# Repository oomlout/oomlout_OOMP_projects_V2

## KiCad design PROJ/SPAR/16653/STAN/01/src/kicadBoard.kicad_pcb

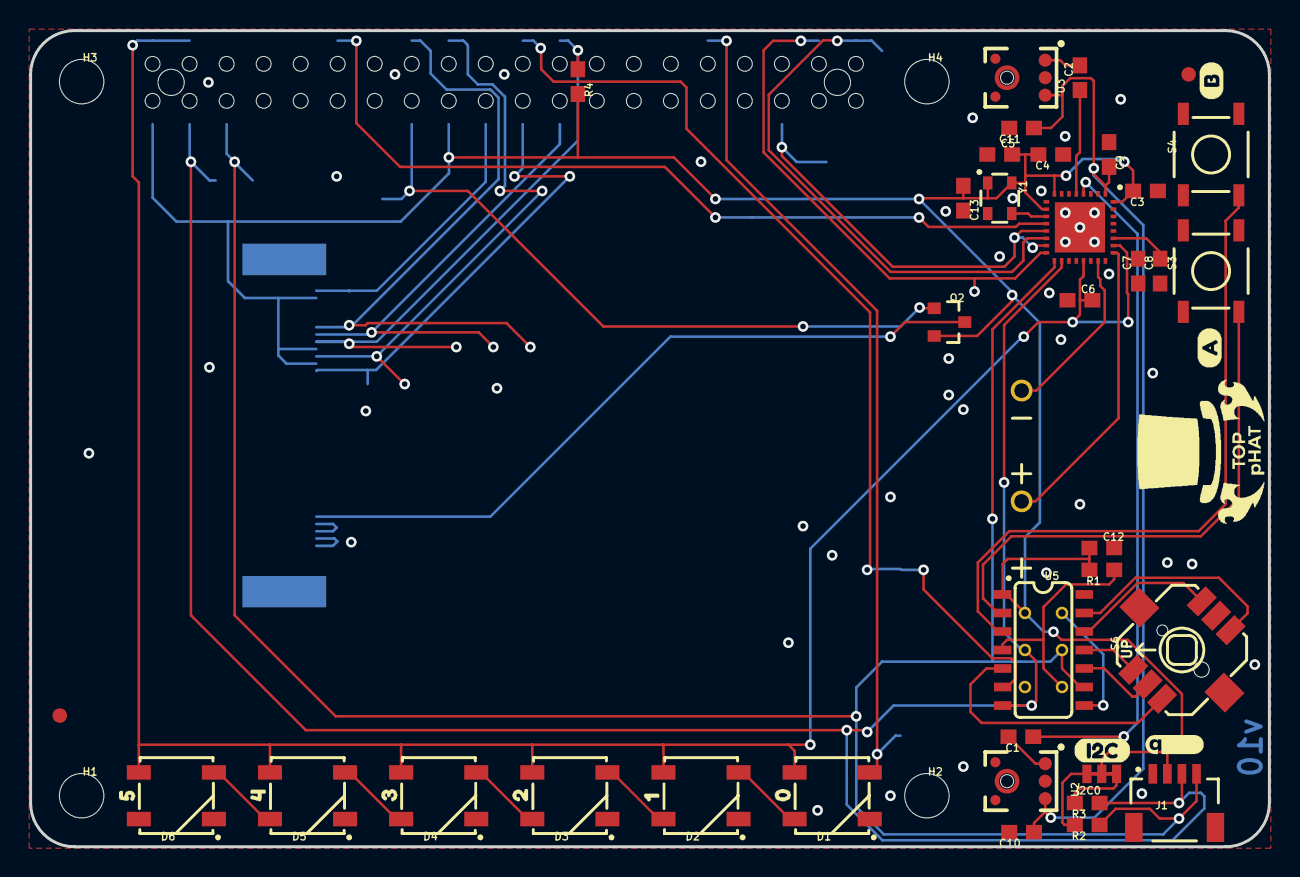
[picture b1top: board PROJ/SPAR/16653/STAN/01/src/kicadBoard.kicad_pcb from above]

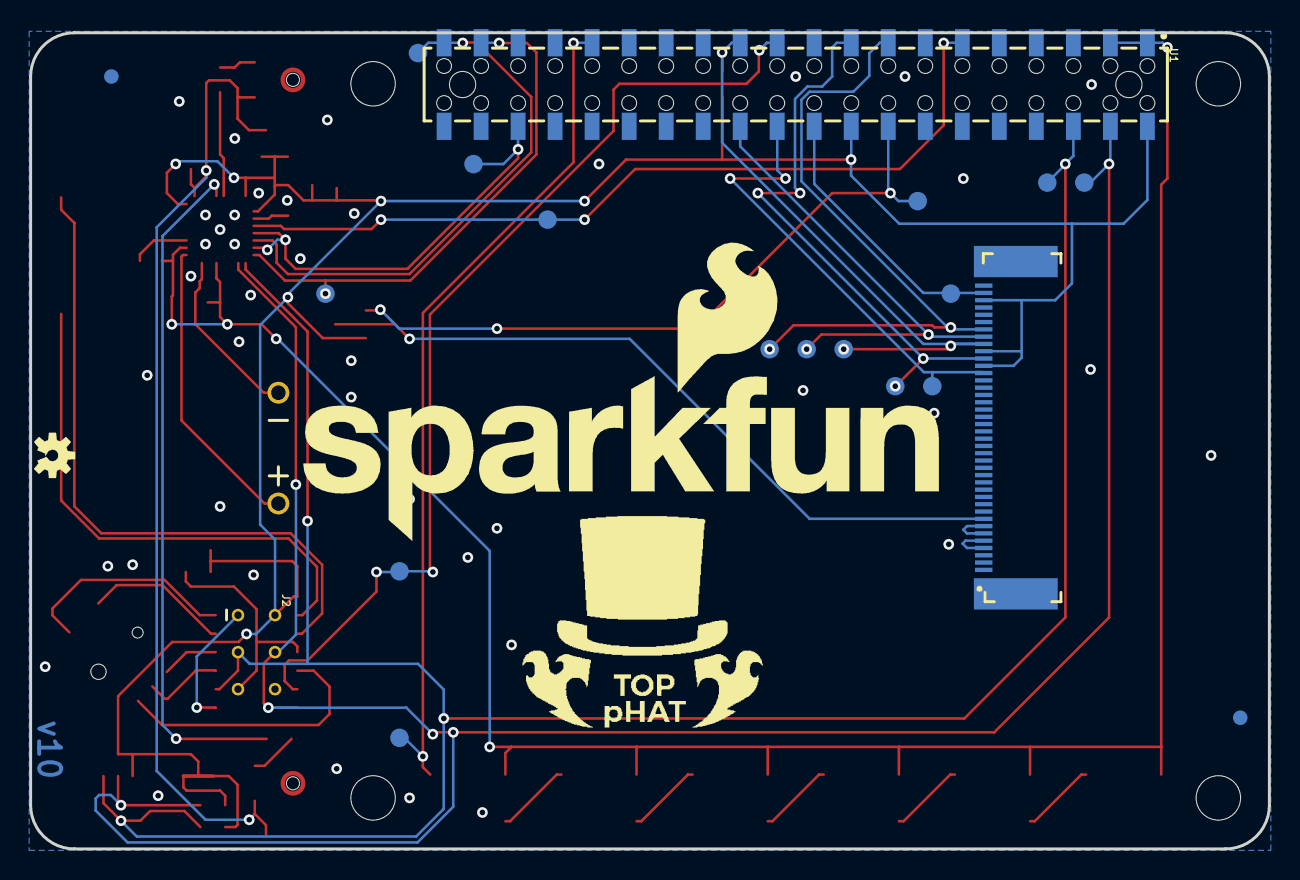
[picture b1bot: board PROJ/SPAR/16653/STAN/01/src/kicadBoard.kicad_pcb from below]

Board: 2 copper layers, 85.0 x 56.0 mm, 76 parts (23 on the bottom side), 44 nets.

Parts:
C1, C2: 2.2uF; 0603
C3, C4, C5, C10, C11, C12: 0.1uF; 0603
C6, C7, C8, C9: 4.7uF; 0603
C13: 10nF; 0603
D1, D2, D3, D4, D5, D6: WS2812B
FD1, FD2, FD3, FD4: FIDUCIAL1X2; FIDUCIAL-1X2
FRAME1: FRAME-LEDGER; CREATIVE_COMMONS
H1, H2, H3, H4: STAND-OFFTIGHT; STAND-OFF-TIGHT
I2C0: JUMPER-SMT_3_2-NC_TRACE_NO-SILK; SMT-JUMPER_3_2-NC_TRACE_NO-SILK
J1: QWIIC; JST04_1MM_RA
J2: AVR_SPI_PROG_3X2TESTPOINTS; 2X3_TEST_POINTS
J3: 2.4" TFT; FPC05040-17204
LOGO2: SFE_LOGO_NAME_FLAME.4_INCH; SFE_LOGO_NAME_FLAME_.4
LOGO3: QWIIC_LOGO_4MM; QWIIC_4MM
LOGO4: OSHW-LOGOS; OSHW-LOGO-S
LS2: CVS-1508; CVS-1508_PCBSPKR
Q2: 1.1A/60V/600mΩ; SOT23-3
R1, R4: 10k; 0603
R2, R3: 4.7k; 0603
S3, S4: MOMENTARY-SWITCH-SPST-SMD-5.2MM-TALL; TACTILE_SWITCH_SMD_5.2MM
S6: Joystick; JOYSTICK_MINI
TP1, TP2, TP3, TP4, TP5, TP6, TP7, TP8, TP9, TP10, TP11, TP12, TP13, TP14, TP15: TEST-POINT3X5; PAD.03X.05
U1: Raspberry Pi Header; RASPBERRY_PI_SHIELD_BOTTOM_ENTRY_NOHOLES
U2, U3: ADMP401
U4: WM8960; QFN-32
U5: ATTINY84; SO14
U$1, U$12: 2020#02#27#PNG
U$3: 00
U$4: 11
U$5: 22
U$6: A0
U$7: B1
U$8: I2C3
U$9: 33
U$10: 44
U$11: 55
Y1: 24 MHz; RESONATOR-SMD-3.2X2.5

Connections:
3.3V: C3.2, C4.2, C5.2, C12.1, C13.1, I2C0.2, J1.2, J2.2, J3.29, J3.31, J3.38, Q2.2, R1.2, R4.2, U1.1, U1.17, U4.8, U4.10, U4.32, U5.1, Y1.1, Y1.4
5V: C6.2, C7.2, D1.1, D2.1, D3.1, D4.1, D5.1, D6.1, U1.2, U1.4, U4.21, U4.26
ADC-DAT: TP10.P$1, U1.38, U4.16
BCLK: TP8.P$1, U1.12, U4.12
BTN_A: S3.3, U5.2
BTN_B: S4.3, U5.3
BTN_CENTER: S6.CTR, U5.10
BTN_DOWN: S6.D, U5.13
BTN_LEFT: S6.C, U5.5
BTN_RIGHT: S6.B, U5.12
BTN_UP: S6.A, U5.11
D/C: J3.30, TP14.P$1, U1.18
DAC-DAT: TP11.P$1, U1.40, U4.14
DAC-LRC: TP9.P$1, U1.35, U4.13, U4.15
GND: C3.1, C4.1, C5.1, C6.1, C7.1, C8.1, C9.1, C10.2, C11.2, C12.2, C13.2, D1.3, D2.3, D3.3, D4.3, D5.3, D6.3, J1.1, J2.6, J3.1, J3.4, J3.5, J3.6, J3.7, J3.11, J3.12, J3.13, J3.14, J3.15, J3.16, J3.17, J3.18, J3.19, J3.20, J3.21, J3.22, J3.23, J3.24, J3.25, J3.26, J3.27, J3.40, S3.1, S4.1, S6.GND, U1.6, U1.9, U1.14, U1.20, U1.25, U1.30, U1.34, U1.39, U2.2, U2.4, U2.6, U3.2, U3.4, U3.6, U4.9, U4.20, U4.24, U4.28, U4.PADDLE, U5.14, Y1.2
LED_DATA: D1.4, TP7.P$1, U1.32
LEFTMIC: C1.2, U2.1
MICBIAS: C9.2, C10.1, C11.1, U2.5, U3.5, U4.1
MISO: J2.1, U5.8
unnamed: D3.2, D4.4
unnamed: D4.2, D5.4
unnamed: D5.2, D6.4
unnamed: J3.8, Q2.3
unnamed: LS2.+, U4.25
unnamed: D1.2, D2.4
unnamed: D2.2, D3.4
unnamed: U4.11, Y1.3
unnamed: I2C0.3, R2.2
unnamed: I2C0.1, R3.2
unnamed: LS2.-, U4.23
unnamed: C1.1, U4.4
unnamed: C2.1, U4.5
unnamed: C8.2, U4.27
RIGHTMIC: C2.2, U3.1
SCK: J3.33, TP5.P$1, U1.23
SCL: J1.4, J2.3, R2.1, TP1.P$1, U1.5, U4.17, U5.9
SDA: J1.3, J2.4, R3.1, TP2.P$1, U1.3, U4.18, U5.7
SDI: J3.39, TP3.P$1, U1.19
SDO: J3.28, TP4.P$1, U1.21
~BKLITE: Q2.1, TP12.P$1, U1.15
~CS: J3.32, R4.1, TP6.P$1, U1.24
~INT: TP15.P$1, U1.22, U5.6
~RST_ATTINY: J2.5, R1.1, U5.4
~RST_SCREEN: J3.34, TP13.P$1, U1.16

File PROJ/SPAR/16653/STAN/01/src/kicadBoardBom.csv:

"Id";"Designator";"Package";"Quantity";"Designation";"Supplier and ref";
1;"FD3,FD1,FD2,FD4";"FIDUCIAL-1X2";4;"FIDUCIAL1X2";;;
2;"U$11";"55";1;"";;;
3;"U$4";"11";1;"";;;
4;"S6";"JOYSTICK_MINI";1;"Joystick";;;
5;"Y1";"RESONATOR-SMD-3.2X2.5";1;"24 MHz";;;
6;"C12,C4,C11,C5,C10,C3";"0603";6;"0.1uF";;;
7;"C7,C6,C9,C8";"0603";4;"4.7uF";;;
8;"U$7";"B1";1;"";;;
9;"D3,D6,D5,D1,D4,D2";"WS2812B";6;"WS2812B";;;
10;"FRAME1";"CREATIVE_COMMONS";1;"FRAME-LEDGER";;;
11;"U$8";"I2C3";1;"";;;
12;"U4";"QFN-32";1;"WM8960";;;
13;"U5";"SO14";1;"ATTINY84";;;
14;"R1,R4";"0603";2;"10k";;;
15;"H1,H4,H2,H3";"STAND-OFF-TIGHT";4;"STAND-OFFTIGHT";;;
16;"U2,U3";"ADMP401";2;"ADMP401";;;
17;"C2,C1";"0603";2;"2.2uF";;;
18;"U$9";"33";1;"";;;
19;"LOGO3";"QWIIC_4MM";1;"QWIIC_LOGO_4MM";;;
20;"U$5";"22";1;"";;;
21;"Q2";"SOT23-3";1;"1.1A/60V/600mΩ";;;
22;"U$6";"A0";1;"";;;
23;"S4,S3";"TACTILE_SWITCH_SMD_5.2MM";2;"MOMENTARY-SWITCH-SPST-SMD-5.2MM-TALL";;;
24;"R2,R3";"0603";2;"4.7k";;;
25;"J1";"JST04_1MM_RA";1;"QWIIC";;;
26;"I2C0";"SMT-JUMPER_3_2-NC_TRACE_NO-SILK";1;"JUMPER-SMT_3_2-NC_TRACE_NO-SILK";;;
27;"LS2";"CVS-1508_PCBSPKR";1;"CVS-1508";;;
28;"U$3";"00";1;"";;;
29;"U$10";"44";1;"";;;
30;"U$1,U$12";"2020#02#27#PNG";2;"";;;
31;"C13";"0603";1;"10nF";;;
32;"TP5,TP10,TP4,TP7,TP1,TP13,TP9,TP11,TP12,TP14,TP15,TP2,TP8,TP3,TP6";"PAD.03X.05";15;"TEST-POINT3X5";;;
33;"U1";"RASPBERRY_PI_SHIELD_BOTTOM_ENTRY_NOHOLES";1;"Raspberry Pi Header";;;
34;"J2";"2X3_TEST_POINTS";1;"AVR_SPI_PROG_3X2TESTPOINTS";;;
35;"J3";"FPC05040-17204";1;"2.4" TFT";;;
36;"LOGO2";"SFE_LOGO_NAME_FLAME_.4";1;"SFE_LOGO_NAME_FLAME.4_INCH";;;
37;"LOGO4";"OSHW-LOGO-S";1;"OSHW-LOGOS";;;

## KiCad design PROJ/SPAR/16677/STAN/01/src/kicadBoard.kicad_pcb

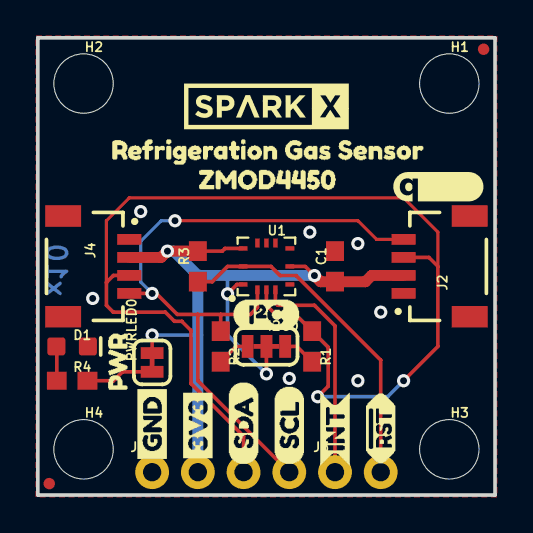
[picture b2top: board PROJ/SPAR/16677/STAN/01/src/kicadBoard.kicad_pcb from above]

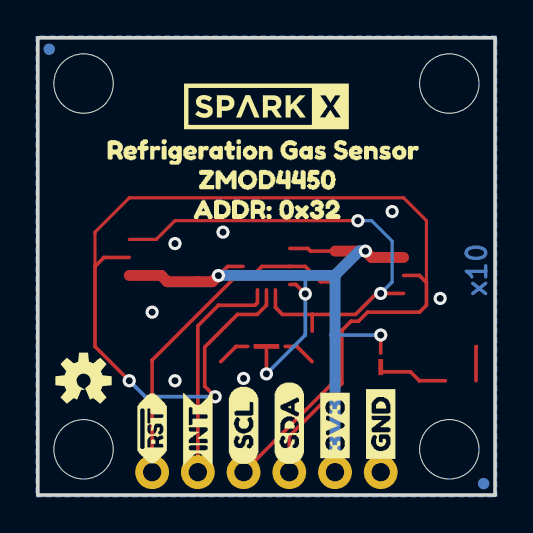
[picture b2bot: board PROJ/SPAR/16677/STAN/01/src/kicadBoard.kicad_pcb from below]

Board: 2 copper layers, 25.4 x 25.4 mm, 46 parts (13 on the bottom side), 10 nets.

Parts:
C1: 0.1uF; 0603
D1: RED; LED-0603
FD1, FD2, FD3, FD4: FIDUCIALUFIDUCIAL; FIDUCIAL-MICRO
FRAME1: FRAME-LETTER; CREATIVE_COMMONS
H1, H2, H3, H4: STAND-OFF
I2C0: JUMPER-SMT_3_2-NC_TRACE_SILK; SMT-JUMPER_3_2-NC_TRACE_SILK
J1: 1X04_NO_SILK
J2, J4: QWIIC_RIGHT_ANGLE; JST04_1MM_RA
J3: 1X02_NO_SILK
LOGO1: OSHW-LOGOS; OSHW-LOGO-S
LOGO2: QWIIC_LOGO_5MM; QWIIC_5MM
PWRLED0: JUMPER-SMT_2_NC_TRACE_SILK; SMT-JUMPER_2_NC_TRACE_SILK
R1, R2, R3: 4.7k; 0603
R4: 1k; 0603
U1: ZMOD4450 Refrigeration Gas Sensor; LGA-12-3X3
U$1, U$2: GND_P
U$3, U$20: ZMOD44501
U$4, U$14: INT_O
U$5, U$6: 3V3_P
U$7, U$8: SDA_IO
U$9, U$10: SCL_IO
U$11: I2C
U$12: PWR_TO
U$13, U$16: !RST_I
U$15, U$17: REFRIGERATION_GAS_SENSOR0
U$18, U$19: SPARKX-MEDIUM
U$21: ADDR#_0X320
U$22: PRODUCTION_INSTRUCTIONS

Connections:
3.3V: C1.1, I2C0.2, J1.2, J2.2, J4.2, PWRLED0.2, R3.2, U1.5, U1.10, U1.12
GND: C1.2, D1.C, J1.1, J2.1, J4.1, U1.6, U1.7, U1.9
INT: J3.1, U1.3
unnamed: I2C0.3, R1.2
unnamed: D1.A, R4.1
unnamed: I2C0.1, R2.2
unnamed: PWRLED0.1, R4.2
SCL: J1.4, J2.4, J4.4, R2.1, U1.1
SDA: J1.3, J2.3, J4.3, R1.1, U1.2
~RST: J3.2, R3.1, U1.11

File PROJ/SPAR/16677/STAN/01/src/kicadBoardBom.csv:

"Id";"Designator";"Package";"Quantity";"Designation";"Supplier and ref";
1;"FD1,FD3,FD2,FD4";"FIDUCIAL-MICRO";4;"FIDUCIALUFIDUCIAL";;;
2;"H3,H1,H2,H4";"STAND-OFF";4;"STAND-OFF";;;
3;"J1";"1X04_NO_SILK";1;"";;;
4;"U$12";"PWR_TO";1;"";;;
5;"LOGO2";"QWIIC_5MM";1;"QWIIC_LOGO_5MM";;;
6;"C1";"0603";1;"0.1uF";;;
7;"U$4,U$14";"INT_O";2;"";;;
8;"U$5,U$6";"3V3_P";2;"";;;
9;"U$22";"PRODUCTION_INSTRUCTIONS";1;"";;;
10;"PWRLED0";"SMT-JUMPER_2_NC_TRACE_SILK";1;"JUMPER-SMT_2_NC_TRACE_SILK";;;
11;"FRAME1";"CREATIVE_COMMONS";1;"FRAME-LETTER";;;
12;"U$18,U$19";"SPARKX-MEDIUM";2;"";;;
13;"R3,R1,R2";"0603";3;"4.7k";;;
14;"U$13,U$16";"!RST_I";2;"";;;
15;"R4";"0603";1;"1k";;;
16;"D1";"LED-0603";1;"RED";;;
17;"U$9,U$10";"SCL_IO";2;"";;;
18;"U$3,U$20";"ZMOD44501";2;"";;;
19;"I2C0";"SMT-JUMPER_3_2-NC_TRACE_SILK";1;"JUMPER-SMT_3_2-NC_TRACE_SILK";;;
20;"U$17,U$15";"REFRIGERATION_GAS_SENSOR0";2;"";;;
21;"J4,J2";"JST04_1MM_RA";2;"QWIIC_RIGHT_ANGLE";;;
22;"U$1,U$2";"GND_P";2;"";;;
23;"U1";"LGA-12-3X3";1;"ZMOD4450 Refrigeration Gas Sensor";;;
24;"J3";"1X02_NO_SILK";1;"";;;
25;"U$11";"I2C";1;"";;;
26;"U$7,U$8";"SDA_IO";2;"";;;
27;"LOGO1";"OSHW-LOGO-S";1;"OSHW-LOGOS";;;
28;"U$21";"ADDR#_0X320";1;"";;;

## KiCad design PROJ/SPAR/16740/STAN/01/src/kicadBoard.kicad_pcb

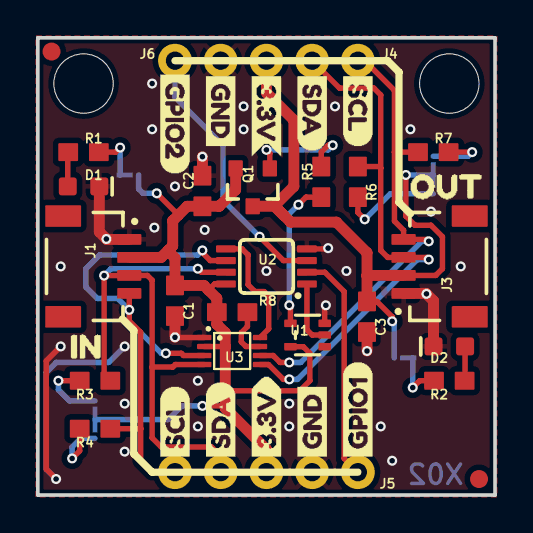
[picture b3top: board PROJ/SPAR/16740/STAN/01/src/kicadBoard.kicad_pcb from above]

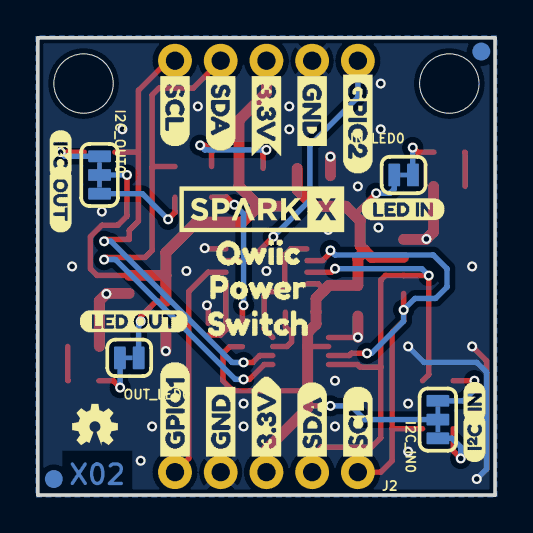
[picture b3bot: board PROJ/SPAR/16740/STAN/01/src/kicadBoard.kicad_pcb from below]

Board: 2 copper layers, 25.4 x 25.4 mm, 67 parts (28 on the bottom side), 22 nets.

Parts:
C1, C3: 0.1uF; 0603
C2: 10uF; 0603
D1: RED; LED-0603
D2: GREEN; LED-0603
FRAME1: FRAME-LETTER; CREATIVE_COMMONS
I2C_IN0, I2C_OUT0: JUMPER-SMT_3_2-NC_TRACE_SILK; SMT-JUMPER_3_2-NC_TRACE_SILK
IN_LED0: IN_LED; SMT-JUMPER_2_NC_TRACE_SILK
J1, J3: Qwiic Right Angle; JST04_1MM_RA
J2, J4: PTH; 1X04_NO_SILK
J5, J6: 1X01_NO_SILK
JP1, JP2, JP5, JP6: FIDUCIAL1X2; FIDUCIAL-1X2
JP3, JP4: STAND-OFF
LOGO1: OSHW-LOGOMINI; OSHW-LOGO-MINI
OUT_LED0: OUT_LED; SMT-JUMPER_2_NC_TRACE_SILK
Q1: 20V/4.2A/52mΩ/1.4W; SOT23-3
R1, R5: 1k; 0603
R2: 470; 0603
R3, R4, R6, R7: 2.2k; 0603
R8: 200k; 0603
U1: 74HC1G04; SOT353
U2: PCA9536; MSOP8
U3: VSSOP_8PIN
U$1, U$28: IN0
U$2: SPARKX-LOGO4; SPARKX-MEDIUM
U$3, U$8, U$13, U$22: GND1
U$4, U$7, U$12, U$23: 3#3V0
U$5, U$11, U$15, U$27: SDA8
U$6, U$9, U$17, U$26: SCL9
U$10, U$18: I_SUPER2_C-()-03
U$14, U$31: OUT0
U$16, U$24: GPIO10
U$19: QWIIC0
U$20, U$25: GPIO20
U$29: LED_IN0
U$30: LED_OUT0
U$32: POWER0
U$34: SWITCH0

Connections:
3.3V: C1.1, C2.1, I2C_IN0.2, IN_LED0.2, J1.2, J2.2, Q1.2, R8.2, U1.5, U2.8, U3.P2
GND: C1.2, C2.2, C3.2, D1.C, D2.C, J1.1, J2.1, J3.1, J4.1, U1.3, U2.4, U3.P1
GPIO0: U1.2, U2.1
GPIO1: J5.1, U2.2
GPIO2: J6.1, U2.3
GPIO3: U2.5, U3.P8
unnamed: I2C_IN0.1, R4.2
unnamed: I2C_IN0.3, R3.2
unnamed: D1.A, R1.1
unnamed: IN_LED0.1, R1.2
unnamed: R5.1, U1.4
unnamed: Q1.1, R5.2
unnamed: OUT_LED0.1, R2.2
unnamed: I2C_OUT0.1, R7.2
unnamed: D2.A, R2.1
unnamed: I2C_OUT0.3, R6.2
unnamed: R8.1, U3.P7
SCL: J1.4, J2.4, R4.1, U2.6, U3.P3
SCL_OUT: J3.4, J4.4, R7.1, U3.P6
SDA: J1.3, J2.3, R3.1, U2.7, U3.P4
SDA_OUT: J3.3, J4.3, R6.1, U3.P5
VOUT: C3.1, I2C_OUT0.2, J3.2, J4.2, OUT_LED0.2, Q1.3

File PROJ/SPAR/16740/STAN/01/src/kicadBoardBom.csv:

"Id";"Designator";"Package";"Quantity";"Designation";"Supplier and ref";
1;"J5,J6";"1X01_NO_SILK";2;"";;;
2;"J1,J3";"JST04_1MM_RA";2;"Qwiic Right Angle";;;
3;"U$25,U$20";"GPIO20";2;"";;;
4;"U$12,U$23,U$7,U$4";"3#3V0";4;"";;;
5;"D2";"LED-0603";1;"GREEN";;;
6;"U$28,U$1";"IN0";2;"";;;
7;"U2";"MSOP8";1;"PCA9536";;;
8;"U3";"VSSOP_8PIN";1;"";;;
9;"J4,J2";"1X04_NO_SILK";2;"PTH";;;
10;"U$17,U$6,U$26,U$9";"SCL9";4;"";;;
11;"C3,C1";"0603";2;"0.1uF";;;
12;"R2";"0603";1;"470";;;
13;"D1";"LED-0603";1;"RED";;;
14;"R7,R6,R3,R4";"0603";4;"2.2k";;;
15;"U$15,U$5,U$27,U$11";"SDA8";4;"";;;
16;"U$24,U$16";"GPIO10";2;"";;;
17;"R1,R5";"0603";2;"1k";;;
18;"U1";"SOT353";1;"74HC1G04";;;
19;"R8";"0603";1;"200k";;;
20;"C2";"0603";1;"10uF";;;
21;"JP4,JP3";"STAND-OFF";2;"STAND-OFF";;;
22;"U$31,U$14";"OUT0";2;"";;;
23;"JP2,JP6,JP5,JP1";"FIDUCIAL-1X2";4;"FIDUCIAL1X2";;;
24;"U$13,U$3,U$8,U$22";"GND1";4;"";;;
25;"Q1";"SOT23-3";1;"20V/4.2A/52mΩ/1.4W";;;
26;"FRAME1";"CREATIVE_COMMONS";1;"FRAME-LETTER";;;
27;"OUT_LED0";"SMT-JUMPER_2_NC_TRACE_SILK";1;"OUT_LED";;;
28;"U$32";"POWER0";1;"";;;
29;"U$30";"LED_OUT0";1;"";;;
30;"I2C_OUT0,I2C_IN0";"SMT-JUMPER_3_2-NC_TRACE_SILK";2;"JUMPER-SMT_3_2-NC_TRACE_SILK";;;
31;"U$29";"LED_IN0";1;"";;;
32;"IN_LED0";"SMT-JUMPER_2_NC_TRACE_SILK";1;"IN_LED";;;
33;"U$2";"SPARKX-MEDIUM";1;"SPARKX-LOGO4";;;
34;"U$19";"QWIIC0";1;"";;;
35;"U$10,U$18";"I_SUPER2_C-()-03";2;"";;;
36;"U$34";"SWITCH0";1;"";;;
37;"LOGO1";"OSHW-LOGO-MINI";1;"OSHW-LOGOMINI";;;

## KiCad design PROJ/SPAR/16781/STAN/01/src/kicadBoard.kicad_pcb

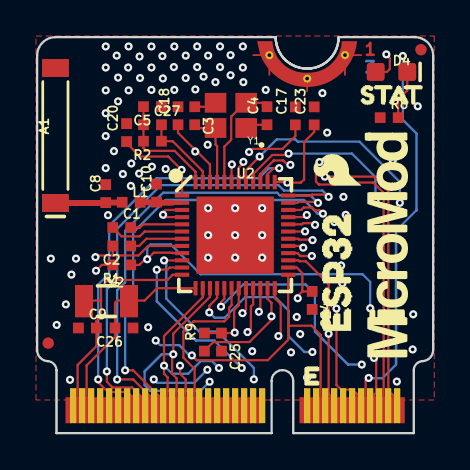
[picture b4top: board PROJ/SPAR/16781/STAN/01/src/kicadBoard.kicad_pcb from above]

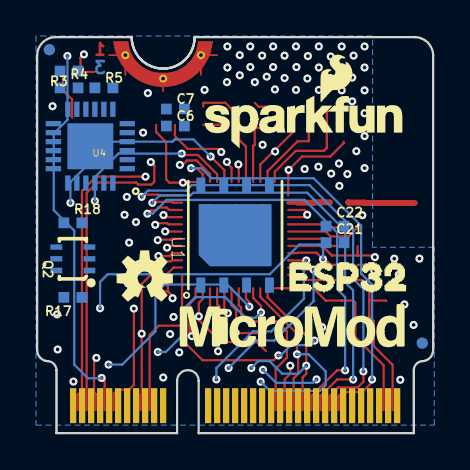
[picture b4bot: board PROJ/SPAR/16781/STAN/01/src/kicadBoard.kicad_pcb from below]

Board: 4 copper layers, 22.0 x 22.0 mm, 53 parts (18 on the bottom side), 54 nets.

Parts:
A1: ANT-2.4GHZ-8.0X1.0MM
C1, C2: 270pF; 0402-TIGHT
C3, C4: 12pF; 0402-TIGHT
C5: 10nF; 0402-TIGHT
C6, C17, C20, C21, C23, C25: 0.1uF; 0402-TIGHT
C7: 4.7uF; 0402-TIGHT
C8, C10: DNP; 0402-TIGHT
C9, C26: 15pF; 0402-TIGHT
C18: 100pF; 0402-TIGHT
C22: 10uF; 0402-TIGHT
C24: 1.0uF; 0402-TIGHT
C27: 3.0nF; 0402-TIGHT
D4: BLUE; LED-0603
FD1, FD2, FD3, FD4: FIDUCIALUFIDUCIAL; FIDUCIAL-MICRO
FRAME1: FRAME-LEDGER; CREATIVE_COMMONS
J1: MICROMOD-2222; M.2-CARD-E-22
L1: 0; 0402-TIGHT
LOGO1: SPECIAL_INSTRUCTIONS-ORDERING; ORDERING_INSTRUCTIONS
LOGO2: SFE_LOGO_NAME_FLAME.1_INCH; SFE_LOGO_NAME_FLAME_.1
LOGO3: OSHW-LOGOS; OSHW-LOGO-S
Q2: MBT3904DW1T1; SC70-6
R1, R9, R17, R18: 10k; 0402-TIGHT
R2: 20k; 0402-TIGHT
R3: 22k; 0402-TIGHT
R4: 33k; 0402-TIGHT
R5: 2.2k; 0402-TIGHT
R8: 1k; 0402-TIGHT
U1: W25QXX128MBIT-6X5; WSON-8-6X5
U2: ESP32; QFN48-0.4MM
U4: CP210X; QFN24
U$1: STAT0
U$2, U$6: MICROMOD_LOGO_.5
U$3, U$7: ESP321
U$4: SFE_LOGO_FLAME_.1
Y1: 40MHz; CRYSTAL-SMD-2X2.5MM
Y2: 32.768kHz; CRYSTAL-SMD-3.2X1.5MM

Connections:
0-~BOOT: J1.11, Q2.6, R9.1, U2.23
2-STAT_LED: D4.A, U2.22
3.3V: C6.1, C7.1, C18.1, C20.1, C21.1, C22.1, C23.1, C25.1, J1.2, J1.74, R1.2, R5.2, R9.2, U2.1, U2.3, U2.4, U2.19, U2.37, U2.43, U2.46, U4.5, U4.6, U4.7
4-I2C_~INT: J1.16, U2.24
5-~CS: J1.55, U2.34
12-PWM1: J1.47, U2.18
13-PWM0: J1.32, U2.20
14-D0: J1.10, U2.17
15-G0: J1.40, U2.21
16-G4/RX1/AUD_IN: J1.19, J1.48, J1.54, U2.25
17-G3/TX1/AUD_OUT: J1.17, J1.46, J1.56, U2.27
18-SCK: J1.57, U2.35
19-CIPO: J1.61, U2.38
21-SDA: J1.12, U2.42
22-SCL: J1.14, U2.39
23-COPI: J1.59, U2.36
25-G1/AUD_LRCLK/SCL1: J1.42, J1.52, J1.53, U2.14
26-G2/AUD_BCLK/SDA1: J1.44, J1.50, J1.51, U2.15
27-D1: J1.18, U2.16
32-G5/RTC: C9.2, J1.73, U2.12, Y2.P$1
33-G6/RTC: C26.2, J1.71, U2.13, Y2.P$2
34-A0: J1.34, U2.10
35-A1: J1.38, U2.11
36: C1.2, U2.5
37: C1.1, U2.6
38: C2.1, U2.7
39-BATT/3: C2.2, J1.49, U2.8
CAP_10N: C5.2, C27.1, R2.2, U2.48
D+: J1.3, U4.3
D-: J1.5, U4.4
DTR: Q2.1, R17.1, U4.23
FLASH_SCK: U1.6, U2.31
FLASH_SCS: U1.1, U2.30
FLASH_SDI: U1.5, U2.33
FLASH_SDO: U1.2, U2.32
FLASH_SHD: U1.7, U2.28
FLASH_SWP: U1.3, U2.29
GND: C3.1, C4.1, C5.1, C6.2, C7.2, C8.2, C9.1, C10.2, C17.2, C18.2, C20.2, C21.2, C22.2, C23.2, C24.2, C25.2, C26.1, J1.1, J1.7, J1.33, J1.36, J1.39, J1.45, J1.75, J1.GND1, J1.GND2, J1.GND3, R4.1, R8.1, U1.4, U2.EP, U4.2, U4.PAD, Y1.P2, Y1.P4
unnamed: D4.C, R8.2
unnamed: R3.1, R4.2, U4.8
unnamed: R5.1, U4.9
unnamed: C27.2, R2.1, U2.47
unnamed: A1.FEED, C8.1, L1.1
unnamed: C10.1, L1.2, U2.2
unnamed: Q2.5, R17.2
unnamed: Q2.2, R18.2
unnamed: C3.2, U2.45, Y1.P1
unnamed: C4.2, U2.44, Y1.P3
RTS: Q2.4, R18.1, U4.19
U0RXD: U2.40, U4.21
U0TXD: U2.41, U4.20
VDD: C17.1, C24.1, U1.8, U2.26
V_USB: J1.9, R3.2
~RESET: J1.6, Q2.3, R1.1, U2.9

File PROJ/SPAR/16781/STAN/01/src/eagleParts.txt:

Partlist

Exported from boardEagle.brd at 20/08/2022 05:38

EAGLE Version 9.6.2 Copyright (c) 1988-2020 Autodesk, Inc.

Assembly variant: 

Part     Value             Package               Library               Position (inch)       Orientation

A1                         ANT-2.4GHZ-8.0X1.0MM  SparkFun-RF           (0.04 0.651)          R90
C1       270pF             0402-TIGHT            SparkFun-Capacitors   (0.185 0.44973228)    R0
C2       270pF             0402-TIGHT            SparkFun-Capacitors   (0.185 0.40938583)    R180
C3       12pF              0402-TIGHT            SparkFun-Capacitors   (0.34472441 0.6942126) R270
C4       12pF              0402-TIGHT            SparkFun-Capacitors   (0.50279528 0.6942126) R90
C5       10nF              0402-TIGHT            SparkFun-Capacitors   (0.25224409 0.71413386) R180
C6       0.1uF             0402-TIGHT            SparkFun-Capacitors   (0.56384252 0.67183465) MR0
C7       4.7uF             0402-TIGHT            SparkFun-Capacitors   (0.56384252 0.709)    MR0
C8       DNP               0402-TIGHT            SparkFun-Capacitors   (0.15 0.524)          R90
C9       15pF              0402-TIGHT            SparkFun-Capacitors   (0.11 0.23)           R0
C10      DNP               0402-TIGHT            SparkFun-Capacitors   (0.261 0.525)         R90
C17      0.1uF             0402-TIGHT            SparkFun-Capacitors   (0.56476378 0.69389764) R90
C18      100pF             0402-TIGHT            SparkFun-Capacitors   (0.30811024 0.69429134) R90
C20      0.1uF             0402-TIGHT            SparkFun-Capacitors   (0.19559055 0.65740157) R90
C21      0.1uF             0402-TIGHT            SparkFun-Capacitors   (0.21456693 0.41653543) MR0
C22      10uF              0402-TIGHT            SparkFun-Capacitors   (0.21456693 0.45275591) MR0
C23      0.1uF             0402-TIGHT            SparkFun-Capacitors   (0.60598425 0.69389764) R90
C24      1.0uF             0402-TIGHT            SparkFun-Capacitors   (0.60161417 0.29027559) R270
C25      0.1uF             0402-TIGHT            SparkFun-Capacitors   (0.40314961 0.1992126) R270
C26      15pF              0402-TIGHT            SparkFun-Capacitors   (0.19 0.23)           R180
C27      3.0nF             0402-TIGHT            SparkFun-Capacitors   (0.25224409 0.67452756) R0
D4       BLUE              LED-0603              SparkFun-LED          (0.775 0.79)          R0
FD1      FIDUCIALUFIDUCIAL FIDUCIAL-MICRO        SparkFun-Aesthetics   (0.02417323 0.19685039) R0
FD2      FIDUCIALUFIDUCIAL FIDUCIAL-MICRO        SparkFun-Aesthetics   (0.02377953 0.19685039) MR0
FD3      FIDUCIALUFIDUCIAL FIDUCIAL-MICRO        SparkFun-Aesthetics   (0.83948819 0.83870079) MR0
FD4      FIDUCIALUFIDUCIAL FIDUCIAL-MICRO        SparkFun-Aesthetics   (0.83948819 0.83870079) R0
J1       MICROMOD-2222     M.2-CARD-E-22         SparkFun-MicroMod     (0.43307087 0)        R0
L1       0                 0402-TIGHT            SparkFun-Resistors    (0.20570866 0.50496063) R0
Q2       MBT3904DW1T1      SC70-6                SparkFun-DiscreteSemi (0.78799213 0.38133071) MR90
R1       10k               0402-TIGHT            SparkFun-Resistors    (0.185 0.36803937)    R180
R2       20k               0402-TIGHT            SparkFun-Resistors    (0.25224409 0.63846457) R180
R3       22k               0402-TIGHT            SparkFun-Resistors    (0.79637795 0.79187402) MR180
R4       33k               0402-TIGHT            SparkFun-Resistors    (0.79637795 0.75523622) MR0
R5       2.2k              0402-TIGHT            SparkFun-Resistors    (0.72015748 0.75523622) MR0
R8       1k                0402-TIGHT            SparkFun-Resistors    (0.77 0.69)           R0
R9       10k               0402-TIGHT            SparkFun-Resistors    (0.3657874 0.19925197) R90
R17      10k               0402-TIGHT            SparkFun-Resistors    (0.78799213 0.297)    MR180
R18      10k               0402-TIGHT            SparkFun-Resistors    (0.78799213 0.46)     MR0
U1       W25QXX128MBIT-6X5 WSON-8-6X5            SparkFun-MicroMod     (0.43307087 0.43307087) MR90
U2       ESP32             QFN48-0.4MM           SparkFun-RF           (0.43307087 0.43307087) R0
U4       CP210X            QFN24                 SparkFun-IC-Comms     (0.74976378 0.62756693) MR180
Y1       40MHz             CRYSTAL-SMD-2X2.5MM   SparkFun-Clocks       (0.42354331 0.6946063) R180
Y2       32.768kHz         CRYSTAL-SMD-3.2X1.5MM SparkFun-Clocks       (0.15161417 0.28870079) R0

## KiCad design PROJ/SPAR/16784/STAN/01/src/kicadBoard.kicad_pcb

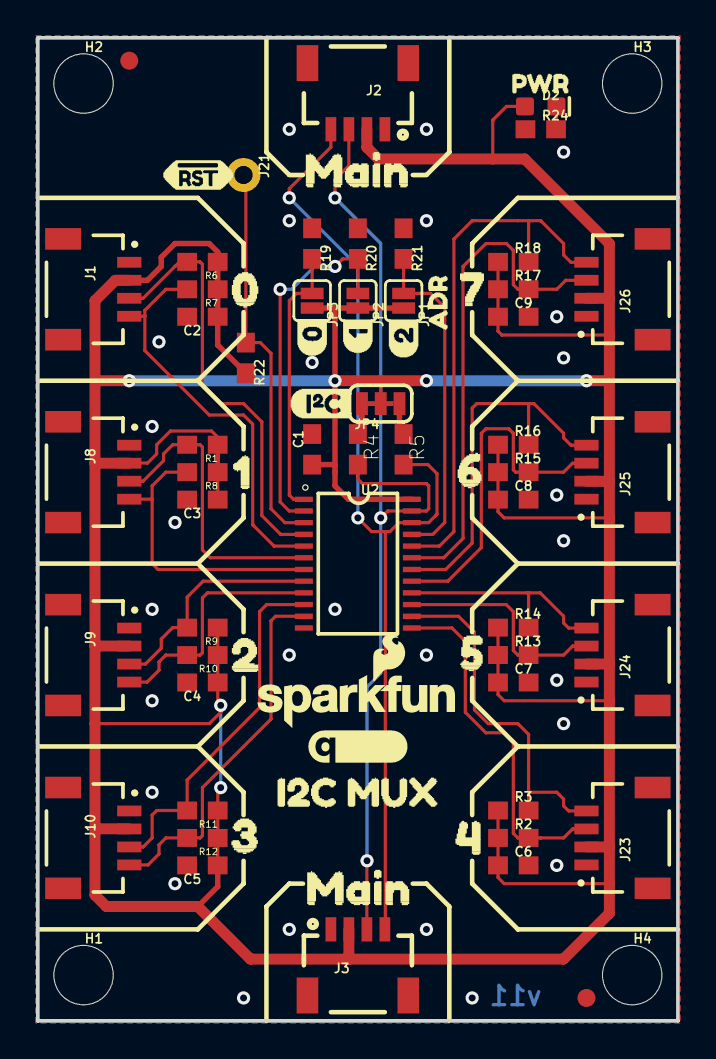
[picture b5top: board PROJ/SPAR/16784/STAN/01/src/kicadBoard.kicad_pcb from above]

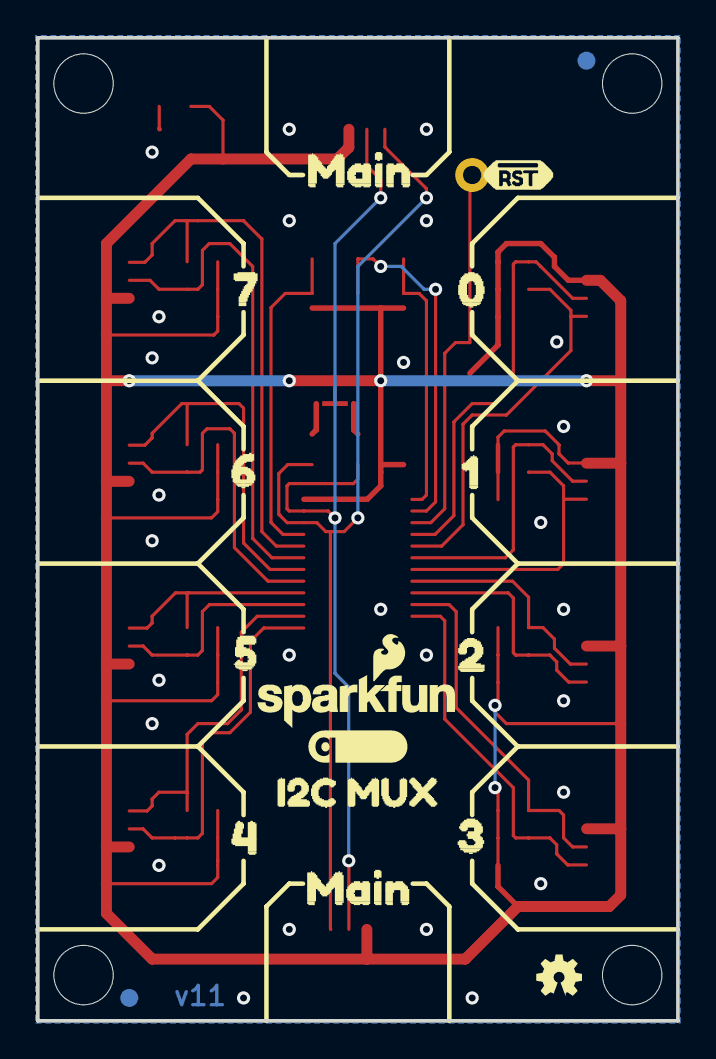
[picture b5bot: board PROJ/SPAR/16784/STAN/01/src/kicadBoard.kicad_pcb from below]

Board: 2 copper layers, 35.6 x 54.6 mm, 94 parts (17 on the bottom side), 27 nets.

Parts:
C1: 0.1uF; 0603
C2, C3, C4, C5, C6, C7, C8, C9: 1.0uF; 0603
D2: RED; LED-0603
FD1, FD2, FD3, FD4: FIDUCIAL1X2; FIDUCIAL-1X2
FRAME1: FRAME-LETTER; CREATIVE_COMMONS
H1, H2, H3, H4: STAND-OFF
J1, J8, J9, J10, J23, J24, J25, J26: QWIIC_RIGHT_ANGLE; JST04_1MM_RA
J2, J3: SMD; 1X04_1MM_RA
J21: 1X01_NO_SILK
JP1, JP2, JP3: JUMPER-SMT_2_NO_SILK; SMT-JUMPER_2_NO_SILK
JP4: JUMPER-SMT_3_2-NC_TRACE_SILK; SMT-JUMPER_3_2-NC_TRACE_SILK
LOGO1: OSHW-LOGOMINI; OSHW-LOGO-MINI
LOGO2: REVISION
R1, R2, R3, R4, R5, R6, R7, R8, R9, R10, R11, R12, R13, R14, R15, R16, R17, R18: 4.7k; 0603
R19, R20, R21, R22: 10k; 0603
R24: 1k; 0603
U2: PCA9548A; TSSOP28
U$1, U$2: SFE_LOGO_NAME_FLAME.1_INCH; SFE_LOGO_NAME_FLAME_.1
U$3, U$15: I2C_MUX8
U$4, U$36: QWIIC_5.5MM
U$5: 04
U$6, U$12: 00
U$7, U$18: 11
U$8, U$19: 22
U$9, U$20: 33
U$10, U$21: 44
U$11, U$22: 55
U$13, U$24: 77
U$14, U$26: !RST_I
U$16, U$25, U$27, U$28: MAIN0
U$17, U$23: 61
U$31: PWR_TO
U$32: 15
U$33: 26
U$34: ADR3
U$35: I#C6

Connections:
3.3V: C1.1, C2.1, C3.1, C4.1, C5.1, C6.1, C7.1, C8.1, C9.1, D2.A, J1.2, J2.2, J3.2, J8.2, J9.2, J10.2, J23.2, J24.2, J25.2, J26.2, JP1.2, JP2.2, JP3.2, JP4.2, R1.1, R2.1, R3.1, R6.1, R7.1, R8.1, R9.1, R10.1, R11.1, R12.1, R13.1, R14.1, R15.1, R16.1, R17.1, R18.1, R22.2, U2.24
ADR0: JP3.1, R19.2, U2.1
ADR1: JP2.1, R20.2, U2.2
ADR2: JP1.1, R21.2, U2.21
GND: C1.2, C2.2, C3.2, C4.2, C5.2, C6.2, C7.2, C8.2, C9.2, J1.1, J2.1, J3.1, J8.1, J9.1, J10.1, J23.1, J24.1, J25.1, J26.1, R19.1, R20.1, R21.1, R24.1, U2.12
MAIN_SCL: J2.4, J3.4, R5.2, U2.22
MAIN_SDA: J2.3, J3.3, R4.2, U2.23
unnamed: D2.C, R24.2
unnamed: JP4.3, R4.1
unnamed: JP4.1, R5.1
SCL0: J1.4, R7.2, U2.5
SCL1: J8.4, R8.2, U2.7
SCL2: J9.4, R10.2, U2.9
SCL3: J10.4, R12.2, U2.11
SCL4: J23.4, R3.2, U2.14
SCL5: J24.4, R14.2, U2.16
SCL6: J25.4, R16.2, U2.18
SCL7: J26.4, R18.2, U2.20
SDA0: J1.3, R6.2, U2.4
SDA1: J8.3, R1.2, U2.6
SDA2: J9.3, R9.2, U2.8
SDA3: J10.3, R11.2, U2.10
SDA4: J23.3, R2.2, U2.13
SDA5: J24.3, R13.2, U2.15
SDA6: J25.3, R15.2, U2.17
SDA7: J26.3, R17.2, U2.19
~RST: J21.1, R22.1, U2.3

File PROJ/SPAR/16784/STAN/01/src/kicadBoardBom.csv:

"Id";"Designator";"Package";"Quantity";"Designation";"Supplier and ref";
1;"J25,J23,J10,J24,J26,J8,J1,J9";"JST04_1MM_RA";8;"QWIIC_RIGHT_ANGLE";;;
2;"U$6,U$12";"00";2;"";;;
3;"JP3,JP2,JP1";"SMT-JUMPER_2_NO_SILK";3;"JUMPER-SMT_2_NO_SILK";;;
4;"C6,C3,C5,C9,C7,C4,C2,C8";"0603";8;"1.0uF";;;
5;"R18,R9,R11,R3,R7,R5,R12,R17,R6,R4,R8,R15,R10,R13,R2,R14,R1,R16";"0603";18;"4.7k";;;
6;"FRAME1";"CREATIVE_COMMONS";1;"FRAME-LETTER";;;
7;"U$8,U$19";"22";2;"";;;
8;"U$10,U$21";"44";2;"";;;
9;"U2";"TSSOP28";1;"PCA9548A";;;
10;"FD1,FD2,FD3,FD4";"FIDUCIAL-1X2";4;"FIDUCIAL1X2";;;
11;"R20,R21,R19,R22";"0603";4;"10k";;;
12;"H4,H2,H1,H3";"STAND-OFF";4;"STAND-OFF";;;
13;"LOGO2";"REVISION";1;"REVISION";;;
14;"U$34";"ADR3";1;"";;;
15;"D2";"LED-0603";1;"RED";;;
16;"J21";"1X01_NO_SILK";1;"";;;
17;"U$16,U$27,U$28,U$25";"MAIN0";4;"";;;
18;"J3,J2";"1X04_1MM_RA";2;"SMD";;;
19;"U$1,U$2";"SFE_LOGO_NAME_FLAME_.1";2;"SFE_LOGO_NAME_FLAME.1_INCH";;;
20;"U$17,U$23";"61";2;"";;;
21;"U$15,U$3";"I2C_MUX8";2;"";;;
22;"U$35";"I#C6";1;"";;;
23;"U$13,U$24";"77";2;"";;;
24;"U$31";"PWR_TO";1;"";;;
25;"U$33";"26";1;"";;;
26;"C1";"0603";1;"0.1uF";;;
27;"U$5";"04";1;"";;;
28;"U$9,U$20";"33";2;"";;;
29;"JP4";"SMT-JUMPER_3_2-NC_TRACE_SILK";1;"JUMPER-SMT_3_2-NC_TRACE_SILK";;;
30;"U$14,U$26";"!RST_I";2;"";;;
31;"U$32";"15";1;"";;;
32;"U$11,U$22";"55";2;"";;;
33;"U$7,U$18";"11";2;"";;;
34;"U$4,U$36";"QWIIC_5.5MM";2;"";;;
35;"R24";"0603";1;"1k";;;
36;"LOGO1";"OSHW-LOGO-MINI";1;"OSHW-LOGOMINI";;;

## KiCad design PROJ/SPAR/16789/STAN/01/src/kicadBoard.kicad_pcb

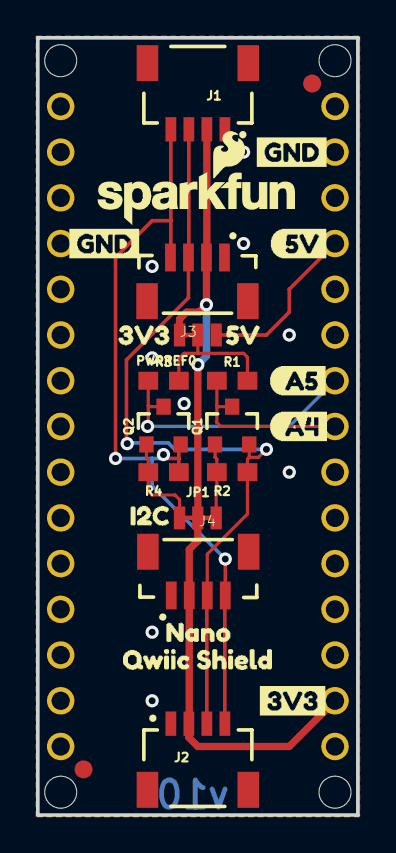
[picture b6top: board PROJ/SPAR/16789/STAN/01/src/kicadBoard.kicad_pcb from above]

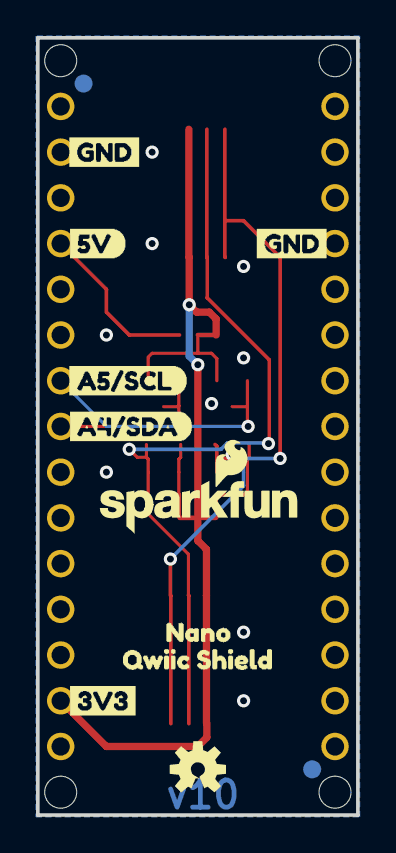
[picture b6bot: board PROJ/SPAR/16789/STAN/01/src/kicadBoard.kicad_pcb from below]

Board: 2 copper layers, 17.8 x 43.2 mm, 44 parts (12 on the bottom side), 10 nets.

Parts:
@HOLE0, @HOLE1, @HOLE2, @HOLE3: (no value)
FD1, FD2, FD3, FD4: FIDUCIAL1X2; FIDUCIAL-1X2
FRAME1: FRAME-LETTER; CREATIVE_COMMONS
J1, J2: QWIIC_RIGHT_ANGLE; JST04_1MM_RA
J3, J4: Vertical Qwiic Connector; JST04_1MM_VERT
J5: NANO_FOOTPRINT; NANO
JP1: JUMPER-SMT_3_2-NC_TRACE_NO-SILK; SMT-JUMPER_3_2-NC_TRACE_NO-SILK
LOGO1: OSHW-LOGOS; OSHW-LOGO-S
LOGO2, LOGO3: SFE_LOGO_NAME_FLAME.1_INCH; SFE_LOGO_NAME_FLAME_.1
PWRREF0: JUMPER-SMT_3_1-NC_TRACE_NO-SILK; SMT-JUMPER_3_1-NC_TRACE_NO-SILK
Q1, Q2: 220mA/50V/3.5Ω; SOT23-3
R1, R2, R3, R4: 4.7k; 0603
U$1, U$15: QWIIC_SHIELD1
U$2, U$14: NANO1
U$3: A4#SDA5
U$4: A5#SCL4
U$5, U$6, U$7, U$8: GND0
U$9: A45
U$10: A56
U$11: I2C6
U$12, U$13: 3V36
U$16: 3V31
U$17, U$18: 5V0
U$19: 5V1

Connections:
3.3V: J1.2, J2.2, J3.2, J4.2, J5.17, JP1.2, PWRREF0.3
5V: J5.27, PWRREF0.1
GND: J1.1, J2.1, J3.1, J4.1, J5.4, J5.29
HV_SCL: J5.24, Q2.3, R3.1
HV_SDA: J5.23, Q1.3, R1.1
IOREF: PWRREF0.2, R1.2, R3.2
SCL: J1.4, J2.4, J3.4, J4.4, Q2.2, R4.1
SCLJUMP: JP1.1, Q2.1, R4.2
SDA: J1.3, J2.3, J3.3, J4.3, Q1.2, R2.1
SDAJUMP: JP1.3, Q1.1, R2.2

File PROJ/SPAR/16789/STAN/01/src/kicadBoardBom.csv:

"Id";"Designator";"Package";"Quantity";"Designation";"Supplier and ref";
1;"PWRREF0";"SMT-JUMPER_3_1-NC_TRACE_NO-SILK";1;"JUMPER-SMT_3_1-NC_TRACE_NO-SILK";;;
2;"@HOLE2,@HOLE1,@HOLE3,@HOLE0";"";4;"";;;
3;"J2,J1";"JST04_1MM_RA";2;"QWIIC_RIGHT_ANGLE";;;
4;"U$6,U$5,U$7,U$8";"GND0";4;"";;;
5;"U$9";"A45";1;"";;;
6;"U$10";"A56";1;"";;;
7;"R4,R3,R1,R2";"0603";4;"4.7k";;;
8;"U$1,U$15";"QWIIC_SHIELD1";2;"";;;
9;"Q2,Q1";"SOT23-3";2;"220mA/50V/3.5Ω";;;
10;"FD1,FD3,FD4,FD2";"FIDUCIAL-1X2";4;"FIDUCIAL1X2";;;
11;"U$17,U$18";"5V0";2;"";;;
12;"JP1";"SMT-JUMPER_3_2-NC_TRACE_NO-SILK";1;"JUMPER-SMT_3_2-NC_TRACE_NO-SILK";;;
13;"FRAME1";"CREATIVE_COMMONS";1;"FRAME-LETTER";;;
14;"J3,J4";"JST04_1MM_VERT";2;"Vertical Qwiic Connector";;;
15;"U$19";"5V1";1;"";;;
16;"J5";"NANO";1;"NANO_FOOTPRINT";;;
17;"U$11";"I2C6";1;"";;;
18;"U$2,U$14";"NANO1";2;"";;;
19;"U$12,U$13";"3V36";2;"";;;
20;"U$16";"3V31";1;"";;;
21;"LOGO2,LOGO3";"SFE_LOGO_NAME_FLAME_.1";2;"SFE_LOGO_NAME_FLAME.1_INCH";;;
22;"LOGO1";"OSHW-LOGO-S";1;"OSHW-LOGOS";;;
23;"U$4";"A5#SCL4";1;"";;;
24;"U$3";"A4#SDA5";1;"";;;

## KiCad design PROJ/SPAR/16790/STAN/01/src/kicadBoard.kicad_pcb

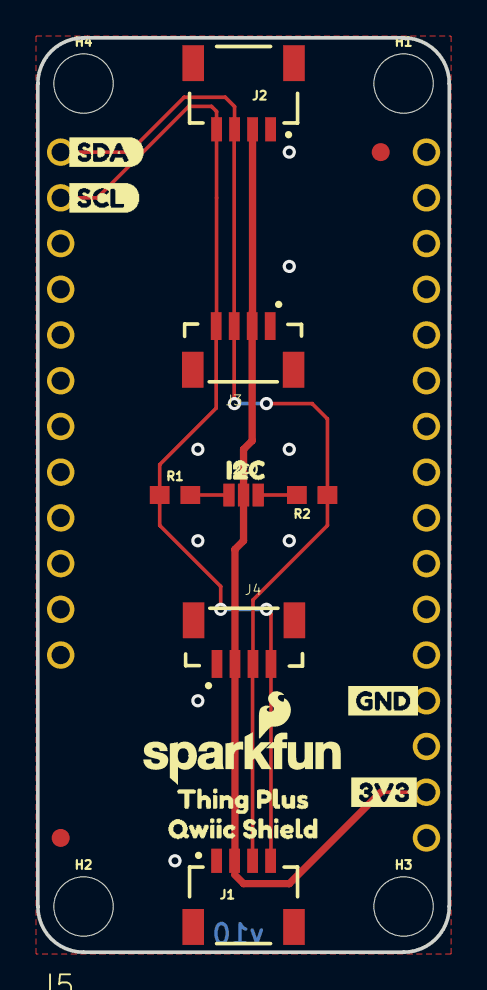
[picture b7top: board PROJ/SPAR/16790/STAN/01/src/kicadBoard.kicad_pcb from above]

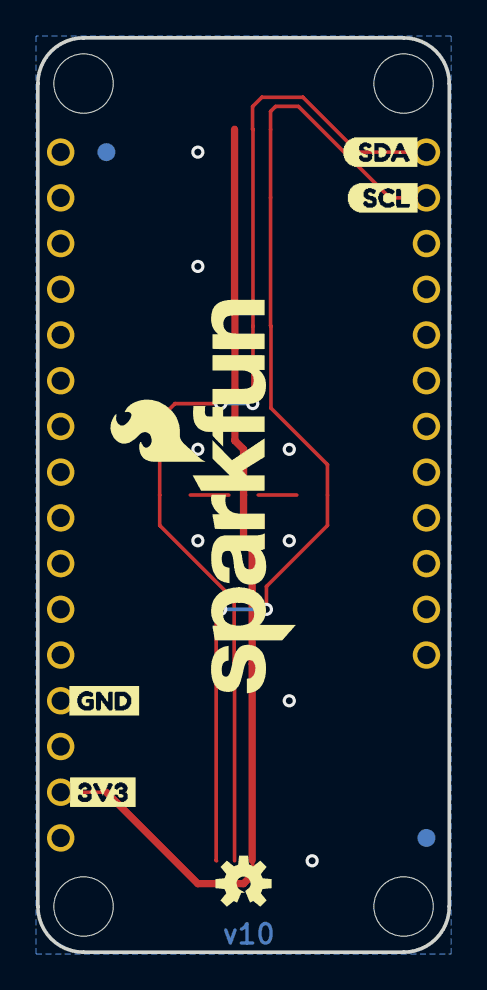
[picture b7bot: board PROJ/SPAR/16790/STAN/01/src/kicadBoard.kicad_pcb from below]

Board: 2 copper layers, 22.9 x 50.8 mm, 32 parts (8 on the bottom side), 6 nets.

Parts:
FD1, FD2, FD3, FD4: FIDUCIAL1X2; FIDUCIAL-1X2
FRAME1: FRAME-LETTER; CREATIVE_COMMONS
H1, H2, H3, H4: STAND-OFF
I2C0: JUMPER-SMT_3_NO_NO-SILK; SMT-JUMPER_3_NO_NO-SILK
J1, J2: QWIIC_RIGHT_ANGLE; JST04_1MM_RA
J3, J4: Vertical Qwiic Connector; JST04_1MM_VERT
J5: THING_PLUS
LOGO1: SFE_LOGO_NAME_FLAME.1_INCH; SFE_LOGO_NAME_FLAME_.1
LOGO2: SFE_LOGO_NAME_FLAME.2_INCH; SFE_LOGO_NAME_FLAME_.2
LOGO3: OSHW-LOGOS; OSHW-LOGO-S
R1, R2: 4.7k; 0603
U$1: THING_PLUS0
U$2: _QWIIC_SHIELD1
U$3, U$4, U$5: 3V36
U$6, U$7: GND0
U$8: I2C5
U$9: SCL1
U$10: SCL3
U$11: SDA0
U$12: SDA2

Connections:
3.3V: I2C0.2, J1.2, J2.2, J3.2, J4.2, J5.27
GND: J1.1, J2.1, J3.1, J4.1, J5.25
unnamed: I2C0.3, R2.2
unnamed: I2C0.1, R1.2
SCL: J1.4, J2.4, J3.4, J4.4, J5.2, R1.1
SDA: J1.3, J2.3, J3.3, J4.3, J5.1, R2.1

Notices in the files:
parts and their libraries:
HTTPS://CREATIVECOMMONS.ORG/LICENSES/BY-SA/4.0
RELEASED UNDER THE CREATIVE COMMONS ATTRIBUTION SHARE-ALIKE 4.0 LICENSE
